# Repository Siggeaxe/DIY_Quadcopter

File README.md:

# Quadcopter Built from Scratch

The purpose of this project is to apply and enhance our knowledge in control theory, signal processing, and electronic design by developing a fully functional quadcopter drone from scratch.

Below are two figures showing the current progress of the project:

| Controller | Quadcopter Drone  |                                                                                                                                                   
| ---           | ---           |                                                                                                                                                   
|   |   |

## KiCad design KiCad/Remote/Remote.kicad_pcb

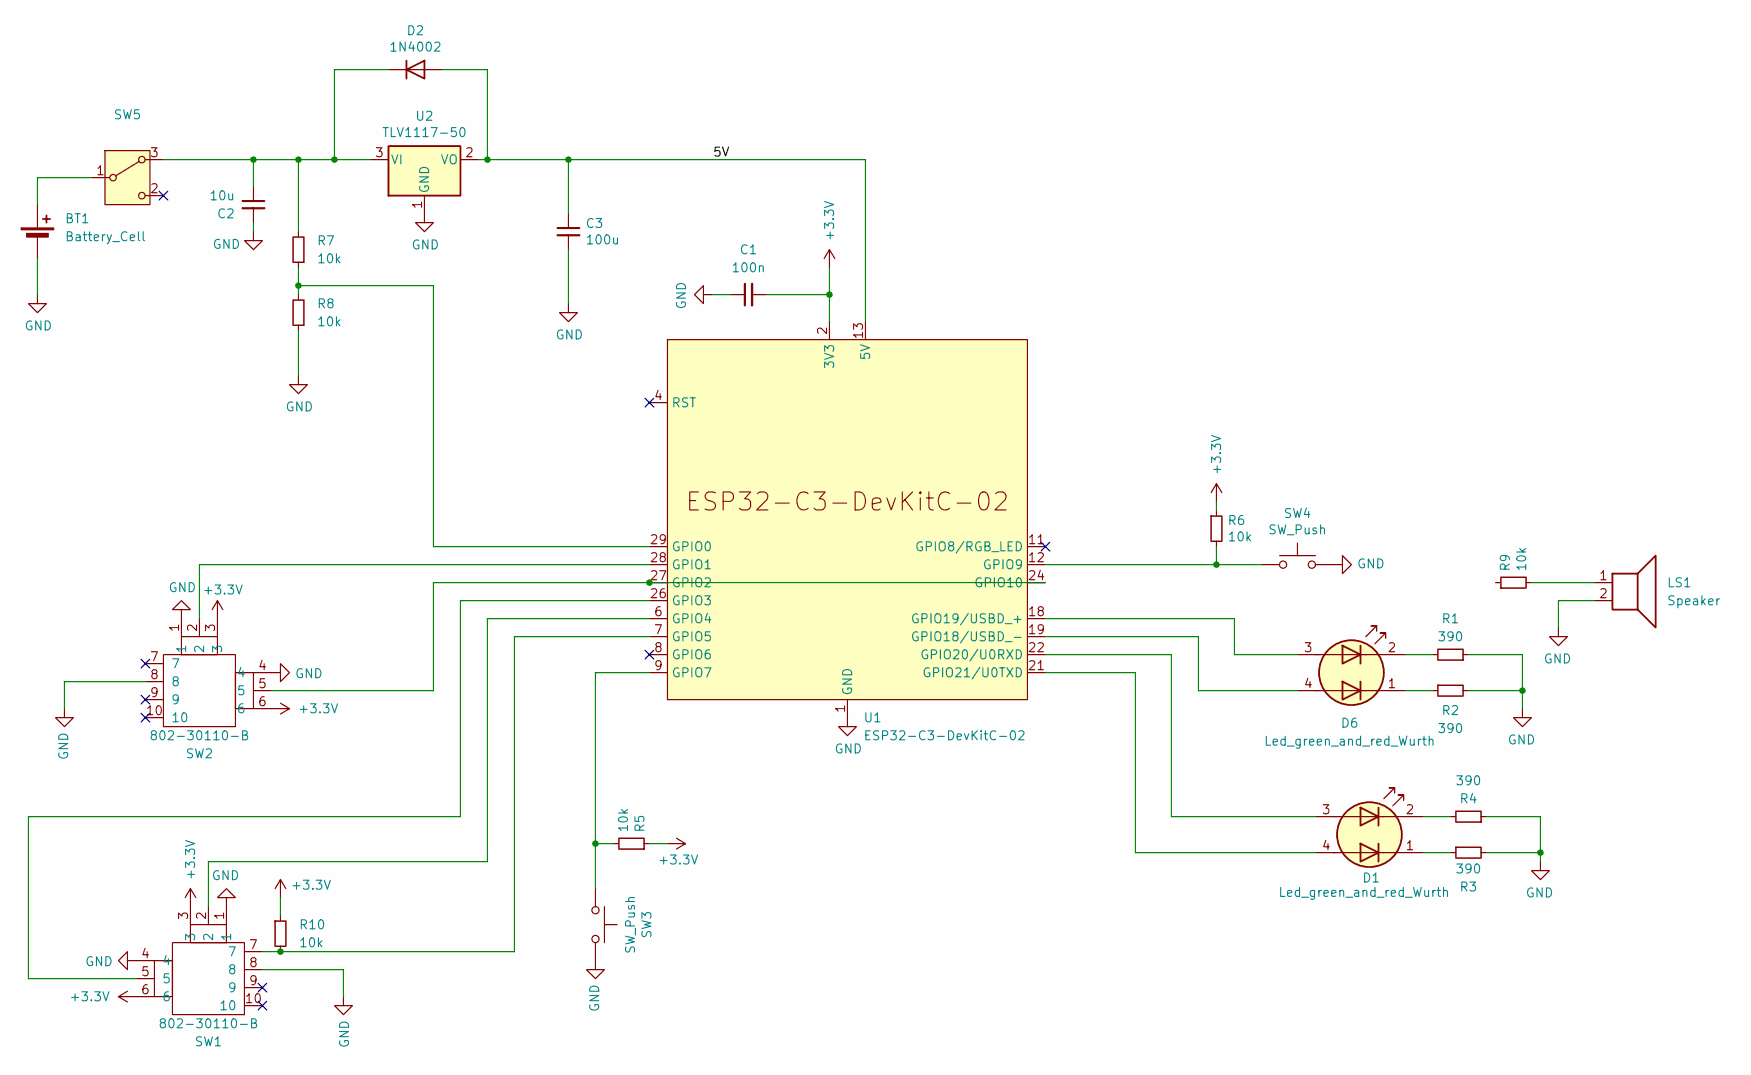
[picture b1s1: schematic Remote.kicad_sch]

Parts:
BT1: Battery_Cell; 9v bat holder
C1: 100n; C_0805_2012Metric_Pad1.18x1.45mm_HandSolder
C2: 10u; C_0805_2012Metric_Pad1.18x1.45mm_HandSolder
C3: 100u; C_0805_2012Metric_Pad1.18x1.45mm_HandSolder
D1, D6: Led_green_and_red_Wurth; Led green and red Wurth
D2: 1N4002; D_0805_2012Metric_Pad1.15x1.40mm_HandSolder
LS1: Speaker; summer 4khz miniatyr
R1, R2, R3, R4: 390; R_0805_2012Metric_Pad1.20x1.40mm_HandSolder
R5, R6, R7, R8, R9, R10: 10k; R_0805_2012Metric_Pad1.20x1.40mm_HandSolder
SW1, SW2: 802-30110-B; Joystick
SW3, SW4: SW_Push; SW_PUSH-12mm
SW5: Skjutomkopplare 1-pol on-on pcb vinklad
U1: ESP32-C3-DevKitC-02
U2: TLV1117-50; SOT230P700X180-4N

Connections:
5V: C3.1, D2.2 (A), U1.13 (5V), U1.14 (5V), U2.2 (VO)
+3.3V: C1.2, R5.1, R6.1, R10.1, SW1.3, SW1.6, SW2.3, SW2.6, U1.2 (3V3), U1.3 (3V3)
GND: BT1.2 (-), C1.1, C2.2, C3.2, LS1.2, R1.1, R2.2, R3.2, R4.1, R8.1, SW1.1, SW1.4, SW1.8, SW2.1, SW2.4, SW2.8, SW3.2, SW4.2, U1.1 (GND), U1.5 (GND), U1.10 (GND), U1.15 (GND), U1.16 (GND), U1.17 (GND), U1.20 (GND), U1.23 (GND), U1.25 (GND), U1.30 (GND), U2.1 (GND)
unnamed: BT1.1 (+), SW5.1 (B)
unnamed: D1.3 (A1), U1.22 (GPIO20/U0RXD)
unnamed: D1.4 (A2), U1.21 (GPIO21/U0TXD)
unnamed: D1.2 (K1), R4.2
unnamed: D1.1 (K2), R3.1
unnamed: C2.1, D2.1 (K), R7.2, SW5.3 (A), U2.3 (VI)
unnamed: D6.3 (A1), U1.18 (GPIO19/USBD_+)
unnamed: D6.4 (A2), U1.19 (GPIO18/USBD_-)
unnamed: D6.2 (K1), R1.2
unnamed: D6.1 (K2), R2.1
unnamed: LS1.1, R9.2
unnamed: R7.1, R8.2, U1.29 (GPIO0)
unnamed: SW2.2, U1.28 (GPIO1)
unnamed: SW1.5, U1.26 (GPIO3)
unnamed: SW1.2, U1.6 (GPIO4)
unnamed: R10.2, SW1.7, U1.7 (GPIO5)
unnamed: R5.2, SW3.1, U1.9 (GPIO7)
unnamed: R6.2, SW4.1, U1.12 (GPIO9)

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
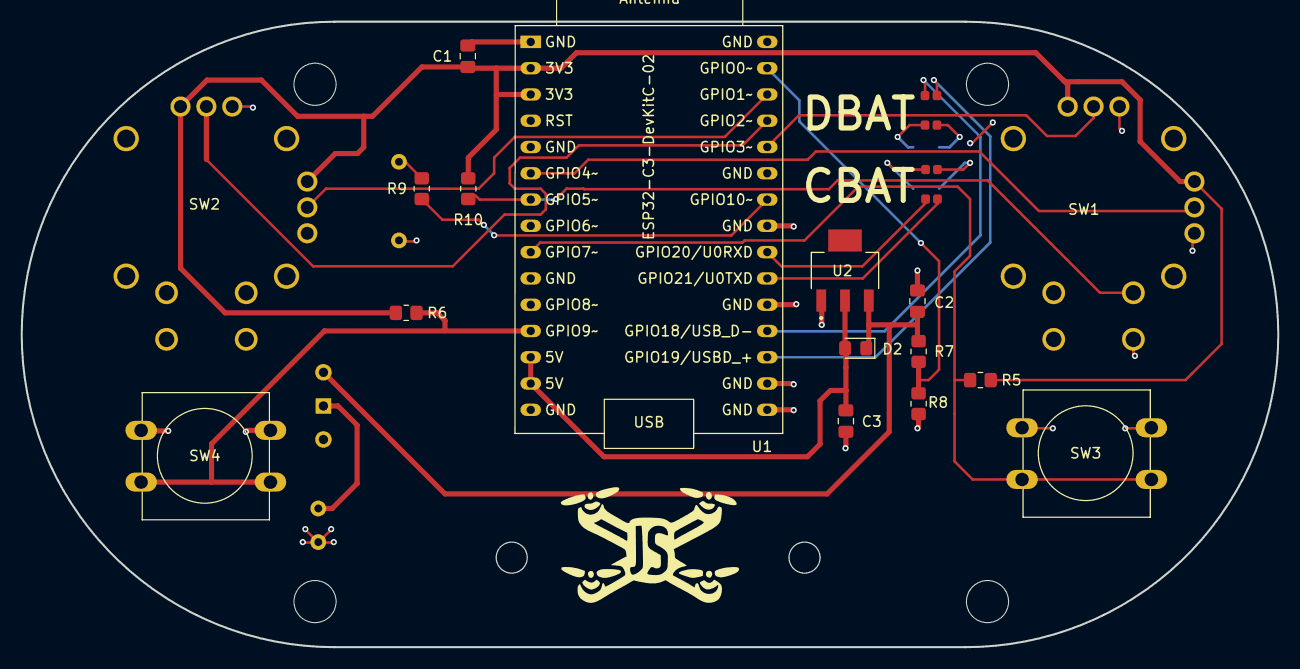
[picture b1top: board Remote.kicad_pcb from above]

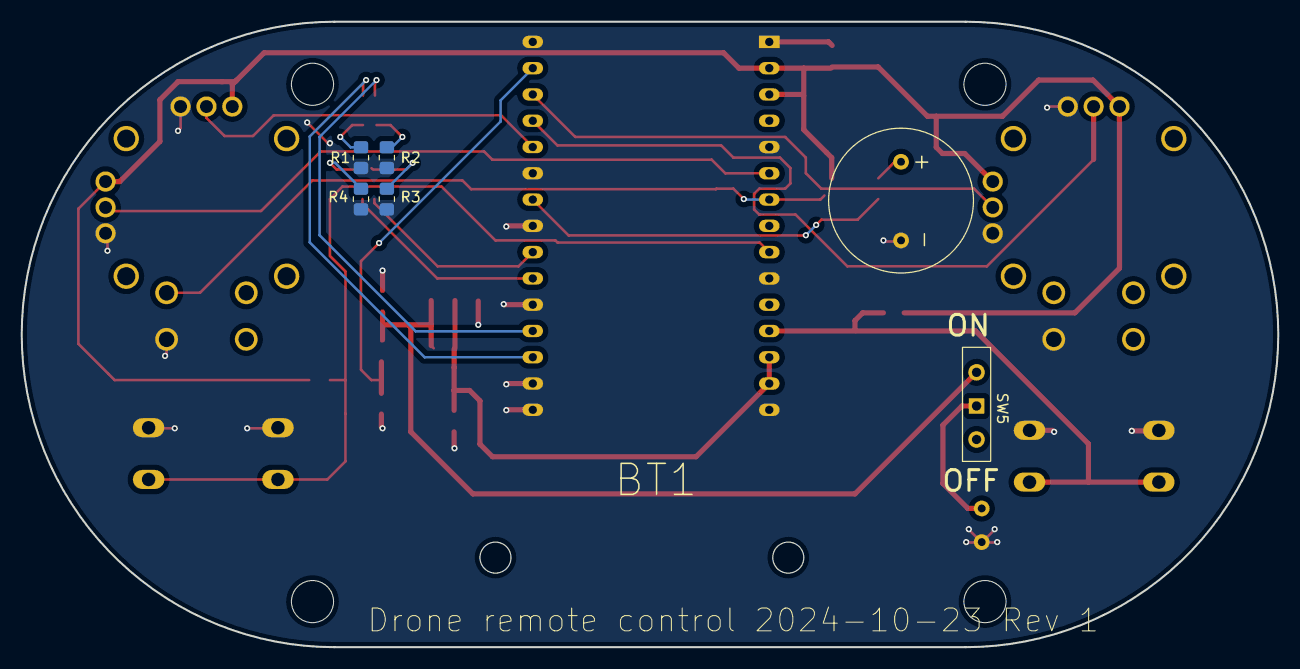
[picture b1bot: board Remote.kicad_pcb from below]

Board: 2 copper layers, 121.5 x 60.5 mm, 25 parts (7 on the bottom side), 23 nets.

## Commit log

2024-09-19 Första utkast av testprogram
    bing bing bong
2024-11-19 Snapshot of curent directory
